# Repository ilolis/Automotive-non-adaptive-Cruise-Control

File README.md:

# Automotive Non Adaptive Cruise Control retrofit for cars
Specifically designed for a Nissan Micra K12 but can be adapted to other cars with existing PCB and firmware changes. 
**DEVICE UNDER DEVELOPMENT. DO NOT USE IT IN A CAR.**

## Description
The goal of this project is to design an aftermarket KIT that is able to hold the specified speed of a car. 

## How it works
**Inputs**

 - Abs speed sensor signal for measuring speed
 - Brake light signal to detect when brake pedal is pressed
 - Actual accelerator pedal signal 
- Various Buttons for controlling the Cruise Control 

**Outputs**
- The accelerator pedal signal that is routed to the car ECU
- Various indicator lights

How it works:

 -  If the Cruise Control is OFF, the actual accelerator pedal signal is routed to the ECU without the intervention of the KIT. 
 - If the Cruise Control is ON, the Arduino reads the speed of the vehicle through the Speed Sensors and generates the correct pedal signal so that the vehicle maintains set speed. The generated (fake) pedal signal is then routed to the ECU.
 - A MUX is used that outputs either the real accelerator pedal signal (when Cruise Control is disabled) or the (fake) signal of the Arduino (if Cruise Control is enabled).  
 - Two relays connected in series act as a MUX while also providing redundancy. In case one relay is stuck the real accelerator pedal will always be routed to the output.
 - The brake pedal deactivates the Cruise Control and immediately (via hardware logic) changes the Select signal of the MUX so that the output changes to the real accelerator pedal. The system will always switch the output to the real accelerator pedal even if the Arduino is frozen. 

## Status
I am currently testing the board, the functionality works as expected with the prototypes. Never use it in car since it is not 100% tested and I can not guarantee that it works flawlessly. Severe injury can be made. More testing has to be done. Software will be the next step.

## License 
Copyright 2021 Lolis Ilias

Permission is hereby granted, free of charge, to any person obtaining a copy of this software and associated documentation files (the "Software"), to deal in the Software without restriction, including without limitation the rights to use, copy, modify, merge, publish, distribute, sublicense, and/or sell copies of the Software, and to permit persons to whom the Software is furnished to do so, subject to the following conditions:

The above copyright notice and this permission notice shall be included in all copies or substantial portions of the Software.

THE SOFTWARE IS PROVIDED "AS IS", WITHOUT WARRANTY OF ANY KIND, EXPRESS OR IMPLIED, INCLUDING BUT NOT LIMITED TO THE WARRANTIES OF MERCHANTABILITY, FITNESS FOR A PARTICULAR PURPOSE AND NONINFRINGEMENT. IN NO EVENT SHALL THE AUTHORS OR COPYRIGHT HOLDERS BE LIABLE FOR ANY CLAIM, DAMAGES OR OTHER LIABILITY, WHETHER IN AN ACTION OF CONTRACT, TORT OR OTHERWISE, ARISING FROM, OUT OF OR IN CONNECTION WITH THE SOFTWARE OR THE USE OR OTHER DEALINGS IN THE SOFTWARE.

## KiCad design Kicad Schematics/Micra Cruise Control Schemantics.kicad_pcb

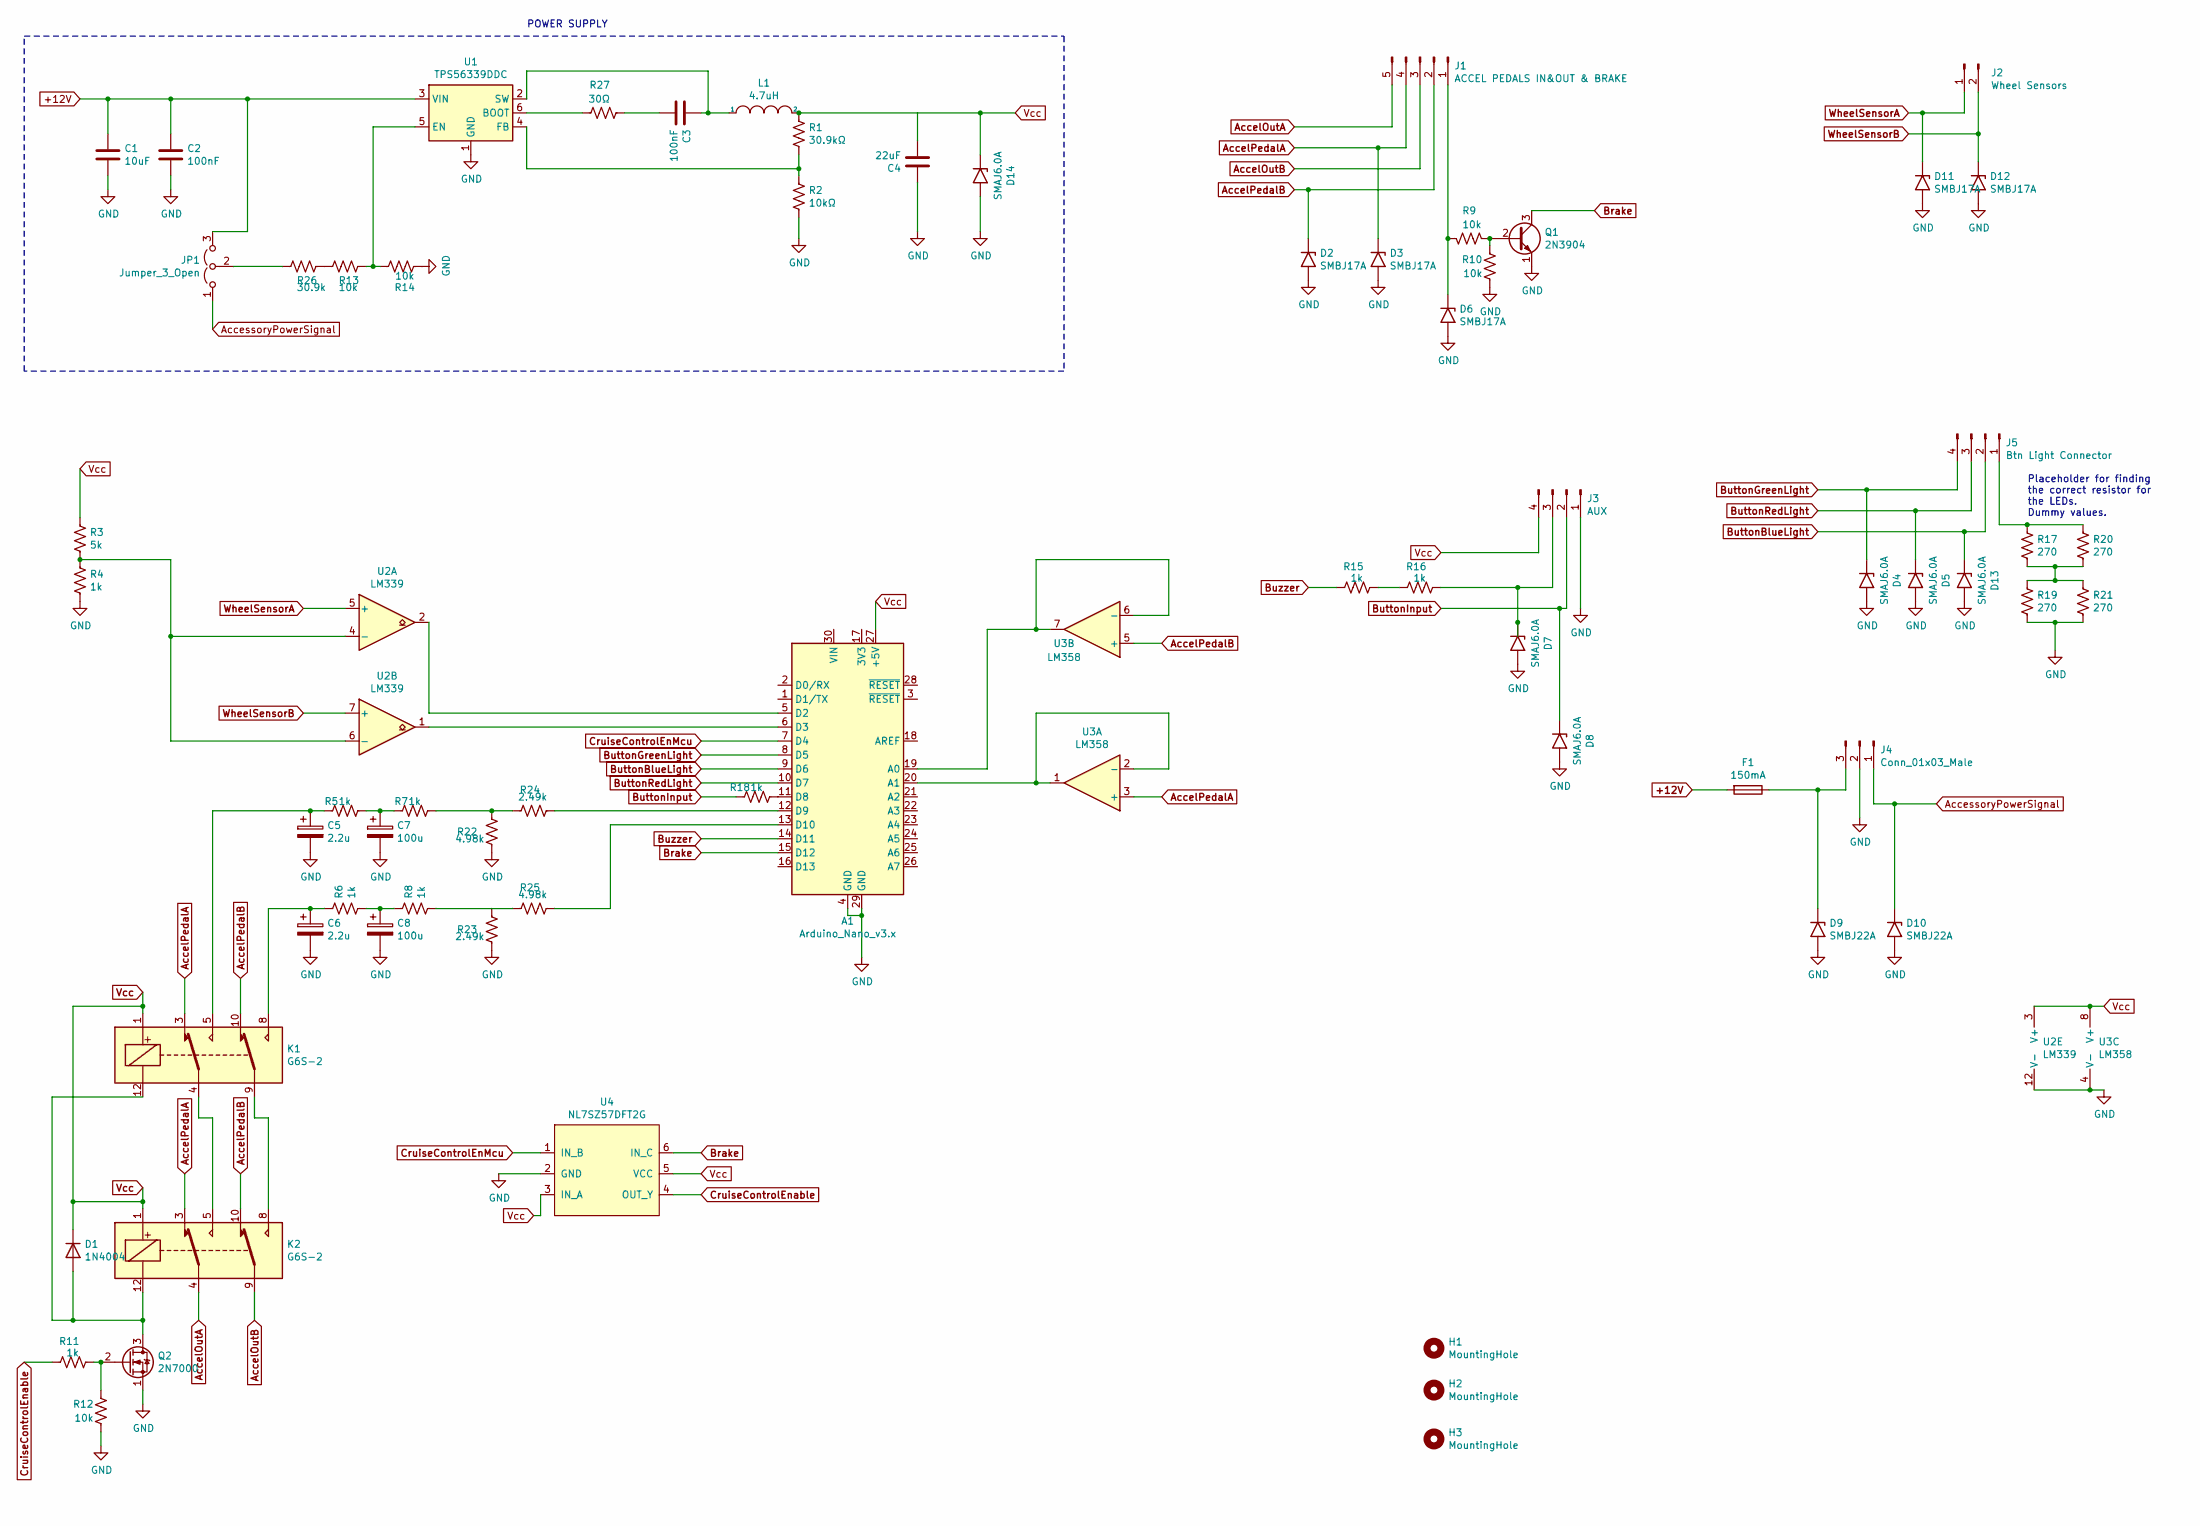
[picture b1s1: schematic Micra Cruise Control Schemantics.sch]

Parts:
A1: Arduino_Nano_v3.x; Arduino_Nano
C1: 10uF; C_1206_3216Metric_Pad1.33x1.80mm_HandSolder
C2, C3: 100nF; C_1206_3216Metric_Pad1.33x1.80mm_HandSolder
C4: 22uF; C_1206_3216Metric_Pad1.33x1.80mm_HandSolder
C5: 2.2u; CP_Radial_D6.3mm_P2.50mm
C6: 2.2u; CP_Radial_D6.3mm_P2.50mm; PartNo EGS2GM2R2E09OT
C7, C8: 100u; CP_Radial_D6.3mm_P2.50mm; PartNo ERS1EM101E11OT
D1: 1N4004; D_DO-41_SOD81_P10.16mm_Horizontal
D2, D3, D6, D11, D12: SMBJ17A; D_SMB_Handsoldering
D4, D5, D7, D8, D13, D14: SMAJ6.0A; D_SMA_Handsoldering
D9, D10: SMBJ22A; D_SMA_Handsoldering
F1: 150mA; C_1206_3216Metric_Pad1.33x1.80mm_HandSolder; LCSC no C369153
H1, H2, H3: MountingHole; MountingHole_3.7mm
J1: ACCEL PEDALS IN&OUT & BRAKE; JST_XH_B5B-XH-A_1x05_P2.50mm_Vertical
J2: Wheel Sensors; JST_XH_B2B-XH-A_1x02_P2.50mm_Vertical
J3: AUX; JST_XH_B4B-XH-A_1x04_P2.50mm_Vertical
J4: Conn_01x03_Male; JST_XH_B3B-XH-A_1x03_P2.50mm_Vertical
J5: Btn Light Connector; JST_XH_B4B-XH-A_1x04_P2.50mm_Vertical
JP1: Jumper_3_Open; SolderJumper-3_P1.3mm_Open_Pad1.0x1.5mm_NumberLabels
K1, K2: G6S-2; Relay_DPDT_Omron_G6S-2F; PartNo G6S-2F DC5
L1: 4.7uH; L_7.3x7.3_H3.5; Part Number YPRH0703-4R7M
Q1: 2N3904; TO-92_Inline; LCSC no C305395
Q2: 2N7000; TO-92_Inline; LCSC no C232838
R1: 30.9kΩ; R_1206_3216Metric_Pad1.30x1.75mm_HandSolder
R2: 10kΩ; R_1206_3216Metric_Pad1.30x1.75mm_HandSolder
R3: 5k; R_1206_3216Metric_Pad1.30x1.75mm_HandSolder
R4, R5, R6, R7, R8, R11, R15, R16, R18: 1k; R_1206_3216Metric_Pad1.30x1.75mm_HandSolder
R9, R10, R12, R13, R14: 10k; R_1206_3216Metric_Pad1.30x1.75mm_HandSolder
R17, R19, R20, R21: 270; R_1206_3216Metric_Pad1.30x1.75mm_HandSolder
R22, R25: 4.98k; R_1206_3216Metric_Pad1.30x1.75mm_HandSolder
R23, R24: 2.49k; R_1206_3216Metric_Pad1.30x1.75mm_HandSolder
R26: 30.9k; R_1206_3216Metric_Pad1.30x1.75mm_HandSolder
R27: 30Ω; R_1206_3216Metric_Pad1.30x1.75mm_HandSolder
U1: TPS56339DDC; TSOT-23-6; MPN TPS56339DDCR
U2: LM339; SOIC-14_3.9x8.7mm_P1.27mm; LCSC no C71036
U3: LM358; SOP-8_3.76x4.96mm_P1.27mm; LCSC no C74525
U4: NL7SZ57DFT2G; SOT-363_SC-70-6_Handsoldering; MPN NL7SZ57DFT2G; LCSC no C94398

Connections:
+12V: C1.1, C2.1, F1.2, JP1.3 (B), U1.3 (VIN)
AccelOutA: J1.5, K2.4
AccelOutB: J1.3, K2.9
AccelPedalA: D3.1 (A1), J1.4, K1.3, K2.3, U3.3 (+)
AccelPedalB: D2.1 (A1), J1.2, K1.10, K2.10, U3.5 (+)
AccessoryPowerSignal: D10.1 (A1), J4.1, JP1.1 (A)
Brake: A1.15 (D12), Q1.3 (C), U4.6 (IN_C)
ButtonBlueLight: A1.9 (D6), D13.1 (A1), J5.2
ButtonGreenLight: A1.8 (D5), D4.1 (A1), J5.4
ButtonInput: D8.1 (A1), J3.2, R18.1
ButtonRedLight: A1.10 (D7), D5.1 (A1), J5.3
Buzzer: A1.14 (D11), R15.1
CruiseControlEnMcu: A1.7 (D4), U4.1 (IN_B)
CruiseControlEnable: R11.1, U4.4 (OUT_Y)
GND: A1.4 (GND), A1.29 (GND), C1.2, C2.2, C4.1, C5.2, C6.2, C7.2, C8.2, D2.2 (A2), D3.2 (A2), D4.2 (A2), D5.2 (A2), D6.2 (A2), D7.2 (A2), D8.2 (A2), D9.2 (A2), D10.2 (A2), D11.2 (A2), D12.2 (A2), D13.2 (A2), D14.2 (A2), J3.1, J4.2, Q1.1 (E), Q2.1 (S), R2.2, R4.2, R10.1, R12.1, R14.1, R19.2, R21.2, R22.1, R23.1, U1.1 (GND), U2.12 (V-), U3.4 (V-), U4.2 (GND)
unnamed: A1.5 (D2), U2.2
unnamed: A1.6 (D3), U2.1
unnamed: A1.11 (D8), R18.2
unnamed: A1.12 (D9), R24.2
unnamed: A1.13 (D10), R25.2
unnamed: A1.19 (A0), U3.6 (-), U3.7
unnamed: A1.20 (A1), U3.1, U3.2 (-)
unnamed: C3.1, L1.1, U1.2 (SW)
unnamed: C3.2, R27.2
unnamed: C5.1, K1.5, R5.1
unnamed: C6.1, K1.8, R6.1
unnamed: C7.1, R5.2, R7.1
unnamed: C8.1, R6.2, R8.1
unnamed: D1.2 (A), K1.12, K2.12, Q2.3 (D)
unnamed: D6.1 (A1), J1.1, R9.2
unnamed: D7.1 (A1), J3.3, R16.2
unnamed: D9.1 (A1), F1.1, J4.3
unnamed: J5.1, R17.1, R20.1
unnamed: JP1.2 (C), R26.2
unnamed: K1.4, K2.5
unnamed: K1.9, K2.8
unnamed: Q1.2 (B), R9.1, R10.2
unnamed: Q2.2 (G), R11.2, R12.2
unnamed: R1.2, R2.1, U1.4 (FB)
unnamed: R3.2, R4.1, U2.4 (-), U2.6 (-)
unnamed: R13.1, R14.2, U1.5 (EN)
unnamed: R13.2, R26.1
unnamed: R15.2, R16.1
unnamed: R17.2, R19.1, R20.2, R21.1
unnamed: R7.2, R22.2, R24.1
unnamed: R8.2, R23.2, R25.1
unnamed: R27.1, U1.6 (BOOT)
Vcc: A1.27 (+5V), C4.2, D1.1 (K), D14.1 (A1), J3.4, K1.1, K2.1, L1.2, R1.1, R3.1, U2.3 (V+), U3.8 (V+), U4.3 (IN_A), U4.5 (VCC)
WheelSensorA: D11.1 (A1), J2.1, U2.5 (+)
WheelSensorB: D12.1 (A1), J2.2, U2.7 (+)

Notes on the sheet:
Placeholder for finding the correct resistor for the LEDs. Dummy values.
POWER SUPPLY

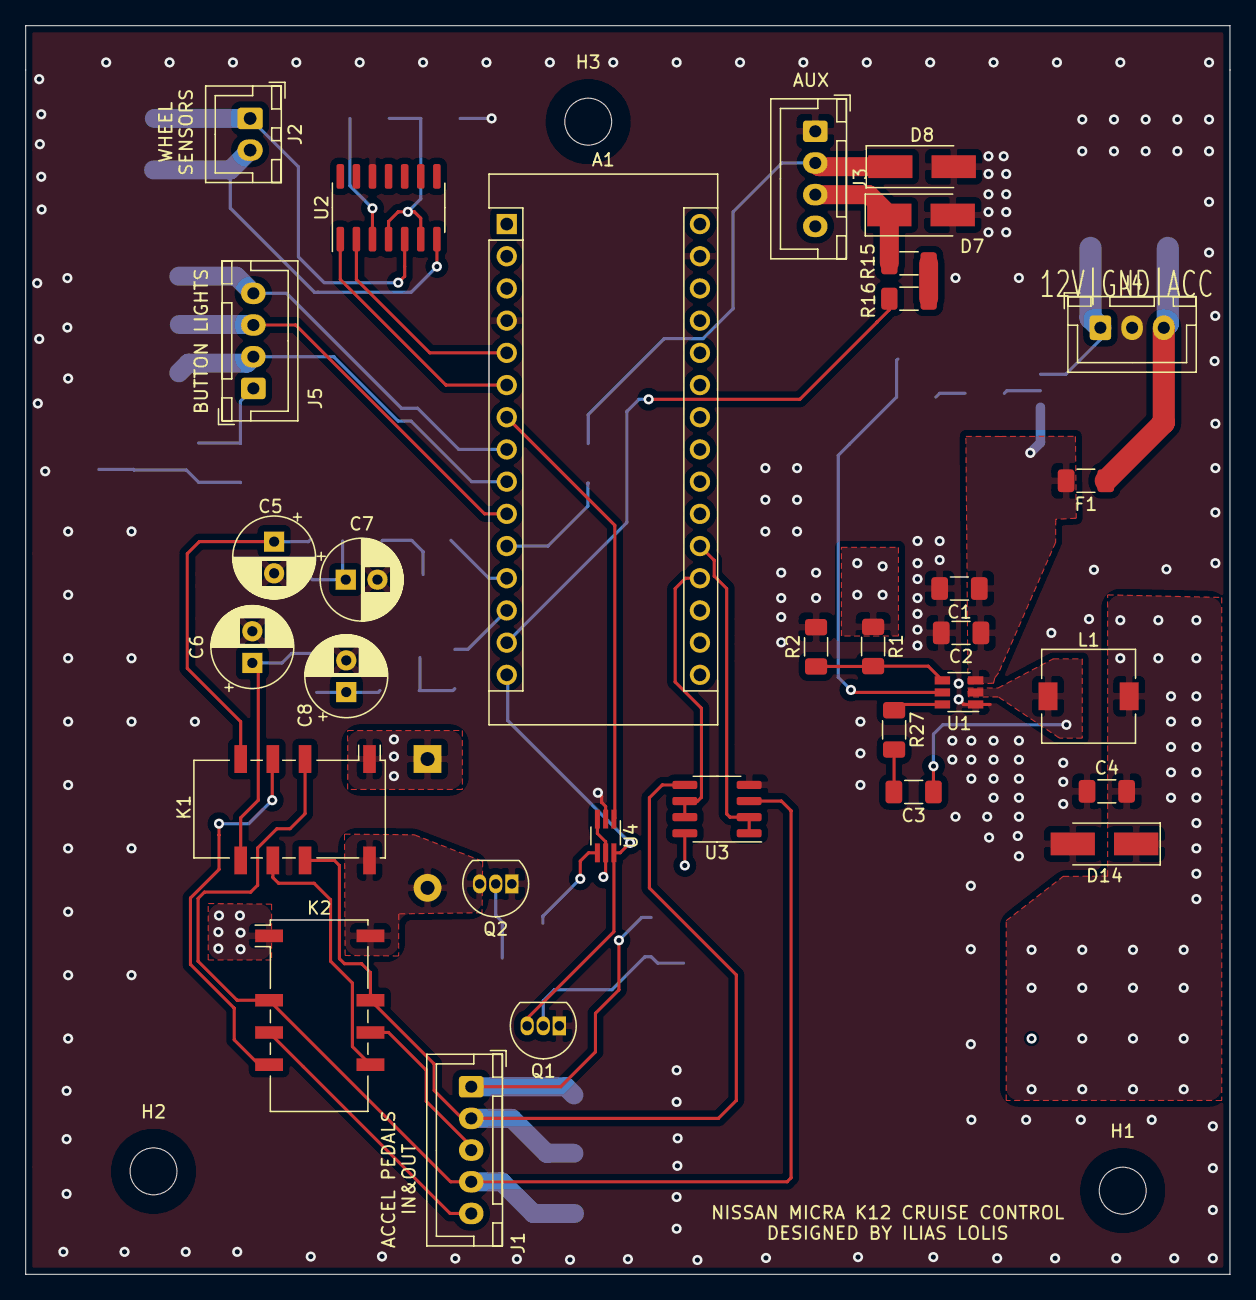
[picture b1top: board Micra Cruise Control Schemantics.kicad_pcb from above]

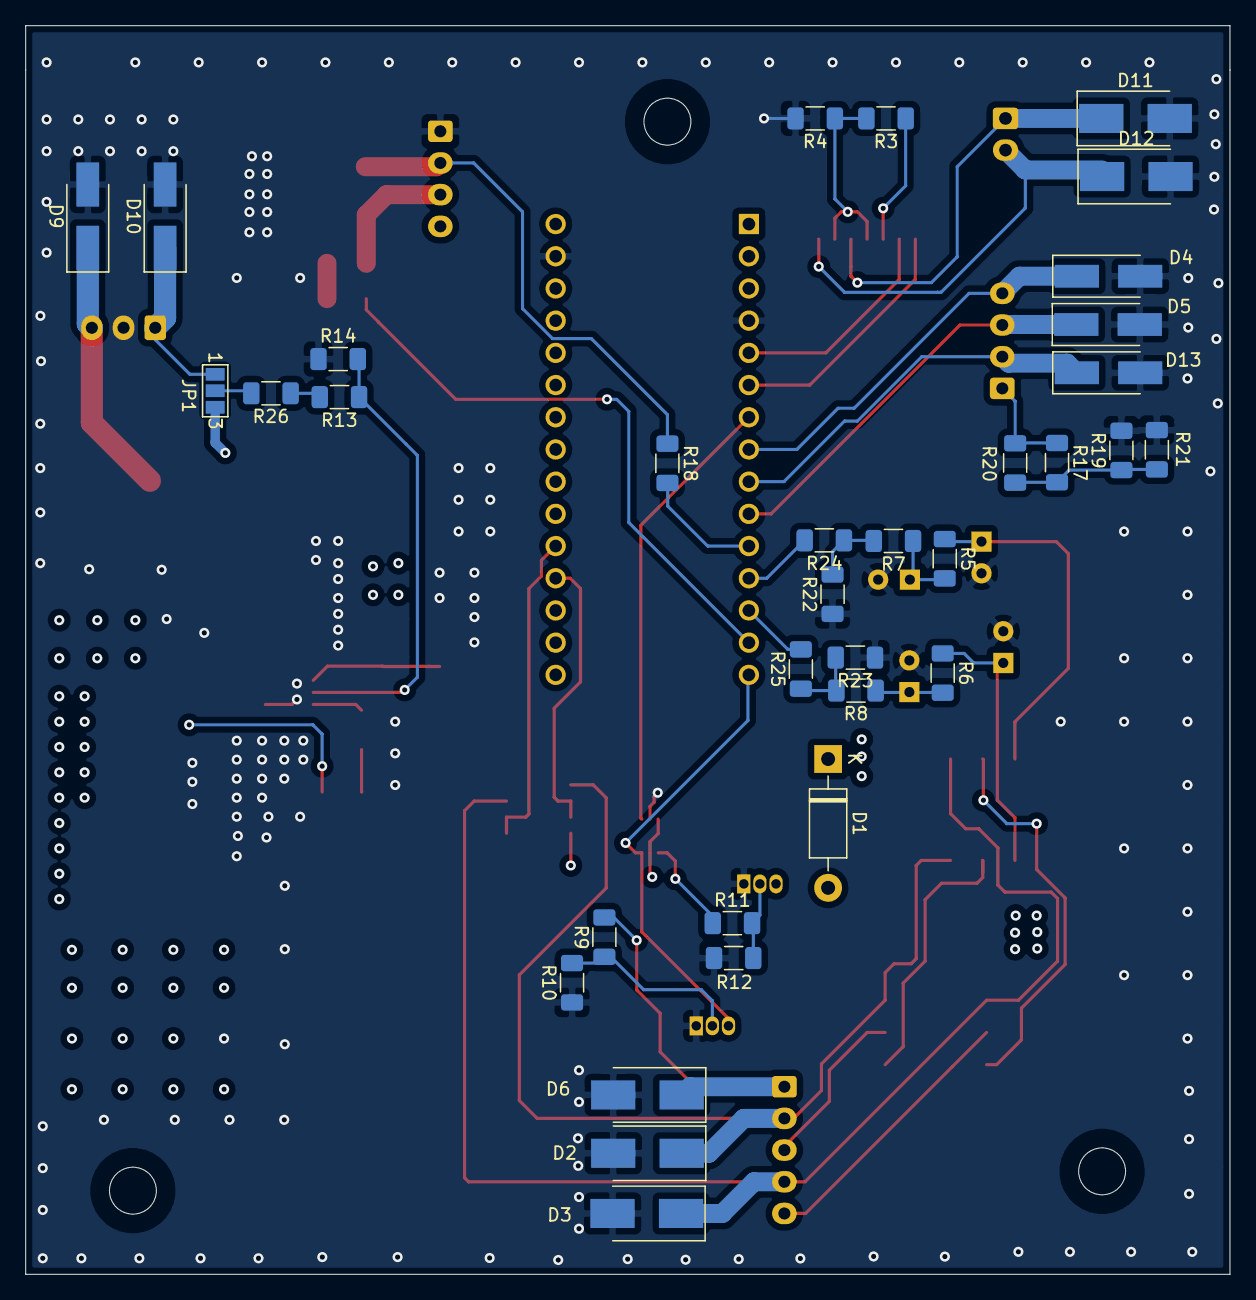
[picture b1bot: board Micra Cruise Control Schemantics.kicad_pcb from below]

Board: 4 copper layers, 95.0 x 98.5 mm, 69 parts (34 on the bottom side), 50 nets.
